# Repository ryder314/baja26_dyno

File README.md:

# baja26_dyno
All files related to the motor dyno built by/for Texas A&M's Baja SAE 2026

The motor dyno makes use of a mechanical hydraulic pump connected to the
engine, which pumps hydraulic fluid around a tank with a restrictor controlled
by a stepper motor.
The designed PCB makes use of an XFW-HX711 module to read a load cell, an A4988
stepper driver for controlling flow restriction, as well as up to two RPM sensors
for engine RPM and eventually for primary/secondary sheave RPM when testing with
the e-CVT.
The design uses a Luckfox Lyra as the devboard to process and store data. This
board runs Buildroot Linux and handles all reading of inputs, calculation of
outputs, and storage/display of results.

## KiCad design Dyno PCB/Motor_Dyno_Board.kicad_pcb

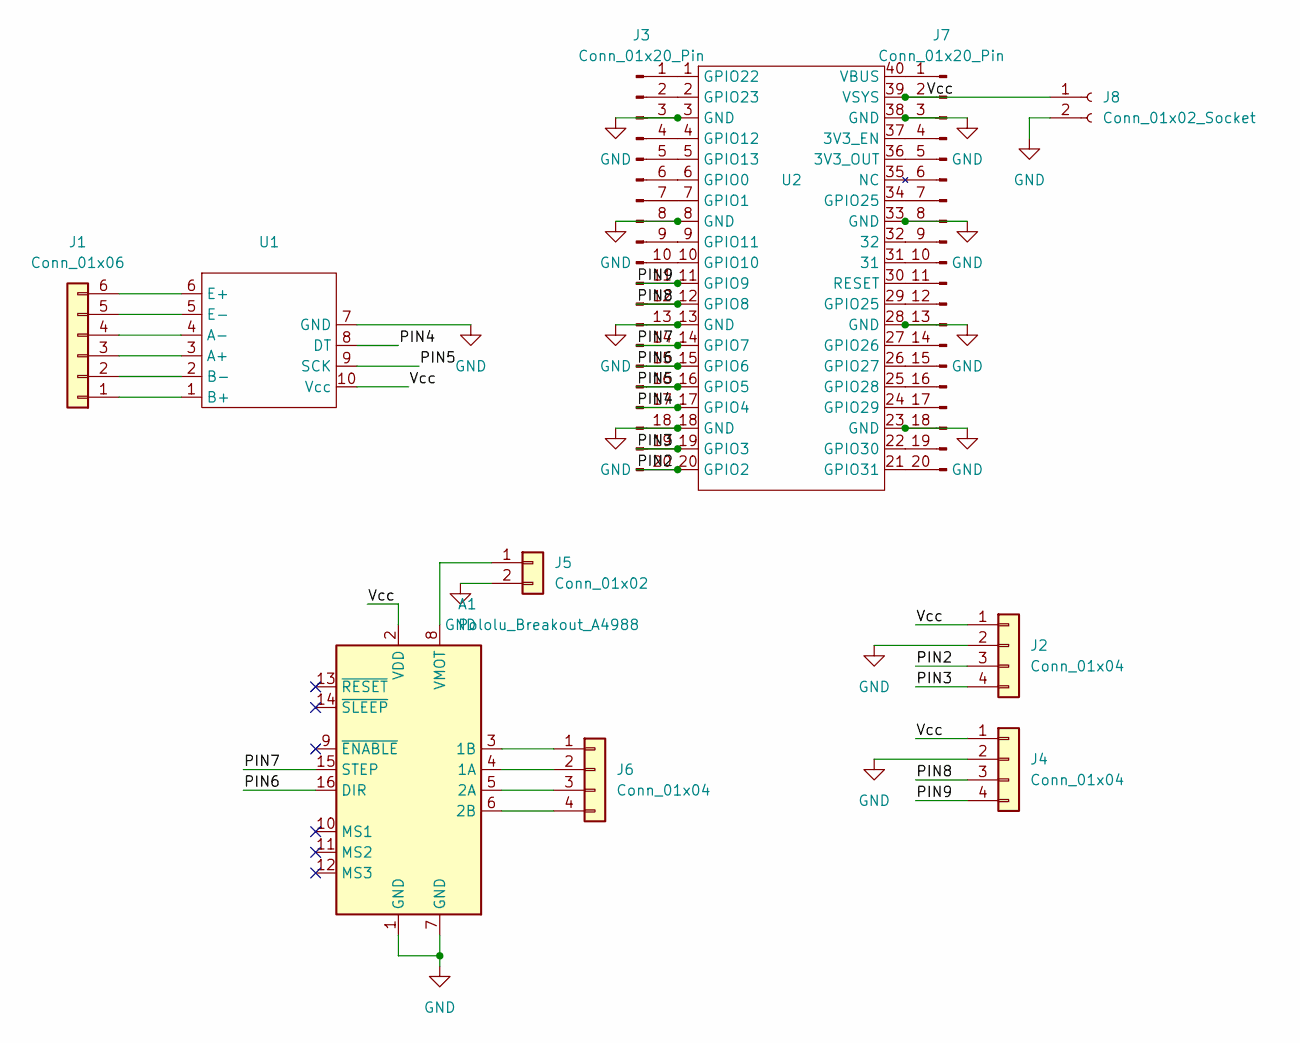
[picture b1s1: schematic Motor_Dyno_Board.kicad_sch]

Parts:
A1: Pololu_Breakout_A4988; Pololu_Breakout-16_15.2x20.3mm
J1: Conn_01x06; JST_XH_B6B-XH-A_1x06_P2.50mm_Vertical
J2, J4, J6: Conn_01x04; JST_XH_B4B-XH-A_1x04_P2.50mm_Vertical
J3, J7: Conn_01x20_Pin; PinHeader_1x20_P2.54mm_Vertical
J5: Conn_01x02; PinHeader_1x02_P2.54mm_Vertical
J8: Conn_01x02_Socket; JST_XH_B2B-XH-A_1x02_P2.50mm_Vertical
U1: XFW_HX711
U2: Untitled

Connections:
/PIN2: J2.3, J3.20, U2.20 (GPIO2)
/PIN3: J2.4, J3.19, U2.19 (GPIO3)
/PIN4: J3.17, U1.8 (DT), U2.17 (GPIO4)
/PIN5: J3.16, U1.9 (SCK), U2.16 (GPIO5)
/PIN6: A1.16 (DIR), J3.15, U2.15 (GPIO6)
/PIN7: A1.15 (STEP), J3.14, U2.14 (GPIO7)
/PIN8: J3.12, J4.3, U2.12 (GPIO8)
/PIN9: J3.11, J4.4, U2.11 (GPIO9)
/Vcc: A1.2 (VDD), J2.1, J4.1, J7.2, J8.1, U1.10 (Vcc), U2.39 (VSYS)
GND: A1.1 (GND), A1.7 (GND), J2.2, J3.3, J3.8, J3.13, J3.18, J4.2, J5.2, J7.3, J7.8, J7.13, J7.18, J8.2, U1.7 (GND), U2.3 (GND), U2.8 (GND), U2.13 (GND), U2.18 (GND), U2.23 (GND), U2.28 (GND), U2.33 (GND), U2.38 (GND)
unnamed: A1.4 (1A), J6.2
unnamed: A1.3 (1B), J6.1
unnamed: A1.5 (2A), J6.3
unnamed: A1.6 (2B), J6.4
unnamed: A1.8 (VMOT), J5.1
unnamed: J1.1, U1.1 (B+)
unnamed: J1.2, U1.2 (B-)
unnamed: J1.3, U1.3 (A+)
unnamed: J1.4, U1.4 (A-)
unnamed: J1.5, U1.5 (E-)
unnamed: J1.6, U1.6 (E+)
unnamed: J3.1, U2.1 (GPIO22)
unnamed: J3.2, U2.2 (GPIO23)
unnamed: J3.4, U2.4 (GPIO12)
unnamed: J3.5, U2.5 (GPIO13)
unnamed: J3.6, U2.6 (GPIO0)
unnamed: J3.7, U2.7 (GPIO1)
unnamed: J3.9, U2.9 (GPIO11)
unnamed: J3.10, U2.10 (GPIO10)
unnamed: J7.1, U2.40 (VBUS)
unnamed: J7.4, U2.37 (3V3_EN)
unnamed: J7.5, U2.36 (3V3_OUT)
unnamed: J7.7, U2.34 (GPIO25)
unnamed: J7.9, U2.32
unnamed: J7.10, U2.31
unnamed: J7.11, U2.30 (RESET)
unnamed: J7.12, U2.29 (GPIO25)
unnamed: J7.14, U2.27 (GPIO26)
unnamed: J7.15, U2.26 (GPIO27)
unnamed: J7.16, U2.25 (GPIO28)
unnamed: J7.17, U2.24 (GPIO29)
unnamed: J7.19, U2.22 (GPIO30)
unnamed: J7.20, U2.21 (GPIO31)

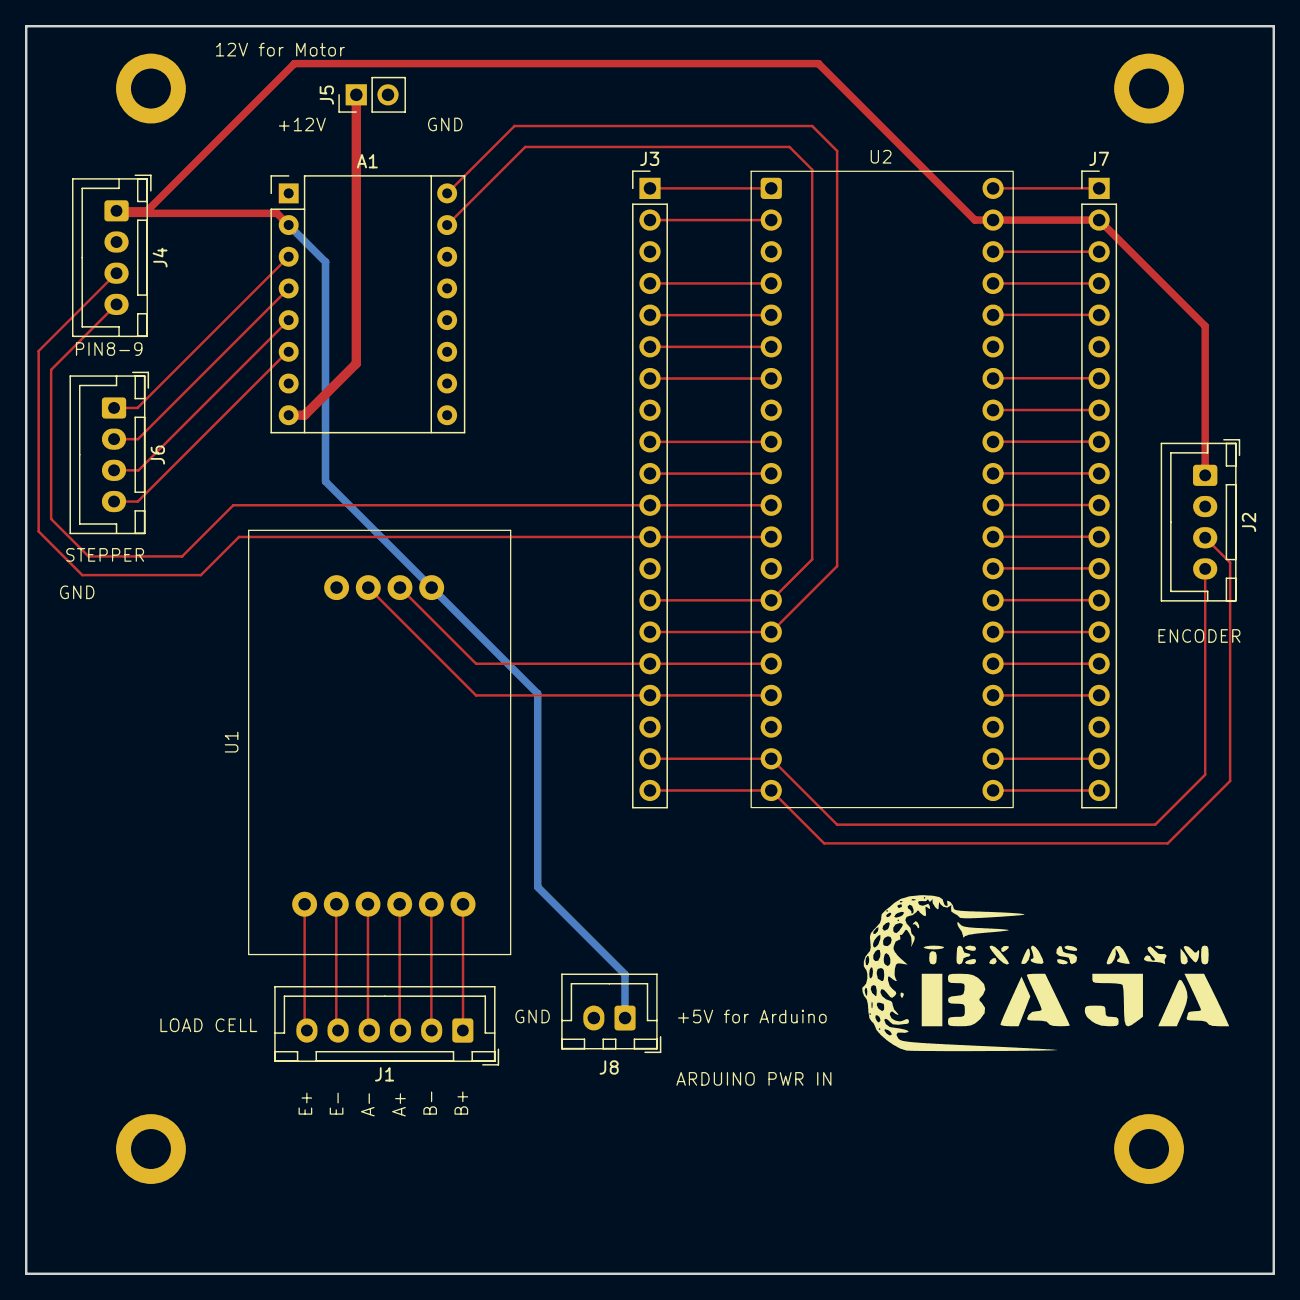
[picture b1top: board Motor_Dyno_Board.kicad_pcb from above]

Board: 2 copper layers, 100.0 x 100.0 mm, 11 parts (0 on the bottom side), 43 nets.

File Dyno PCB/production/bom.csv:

Designator,Footprint,Quantity,Value,LCSC Part #
A1,Pololu_Breakout-16_15.2x20.3mm,1,Pololu_Breakout_A4988,
J1,JST_XH_B6B-XH-A_1x06_P2.50mm_Vertical,1,Conn_01x06,
"J2, J4, J6",JST_XH_B4B-XH-A_1x04_P2.50mm_Vertical,3,Conn_01x04,
"J3, J7",PinHeader_1x20_P2.54mm_Vertical,2,Conn_01x20_Pin,
J5,PinHeader_1x02_P2.54mm_Vertical,1,Conn_01x02,
J8,JST_XH_B2B-XH-A_1x02_P2.50mm_Vertical,1,Conn_01x02_Socket,
U1,XFW_HX711,1,~,
U2,Untitled,1,~,

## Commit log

2025-10-07 Updated readme and added PCB design files from v1, ordered 10/7/25
2025-10-07 Adding picture of PCB for readme
2025-10-07 figuring out how pictures work
